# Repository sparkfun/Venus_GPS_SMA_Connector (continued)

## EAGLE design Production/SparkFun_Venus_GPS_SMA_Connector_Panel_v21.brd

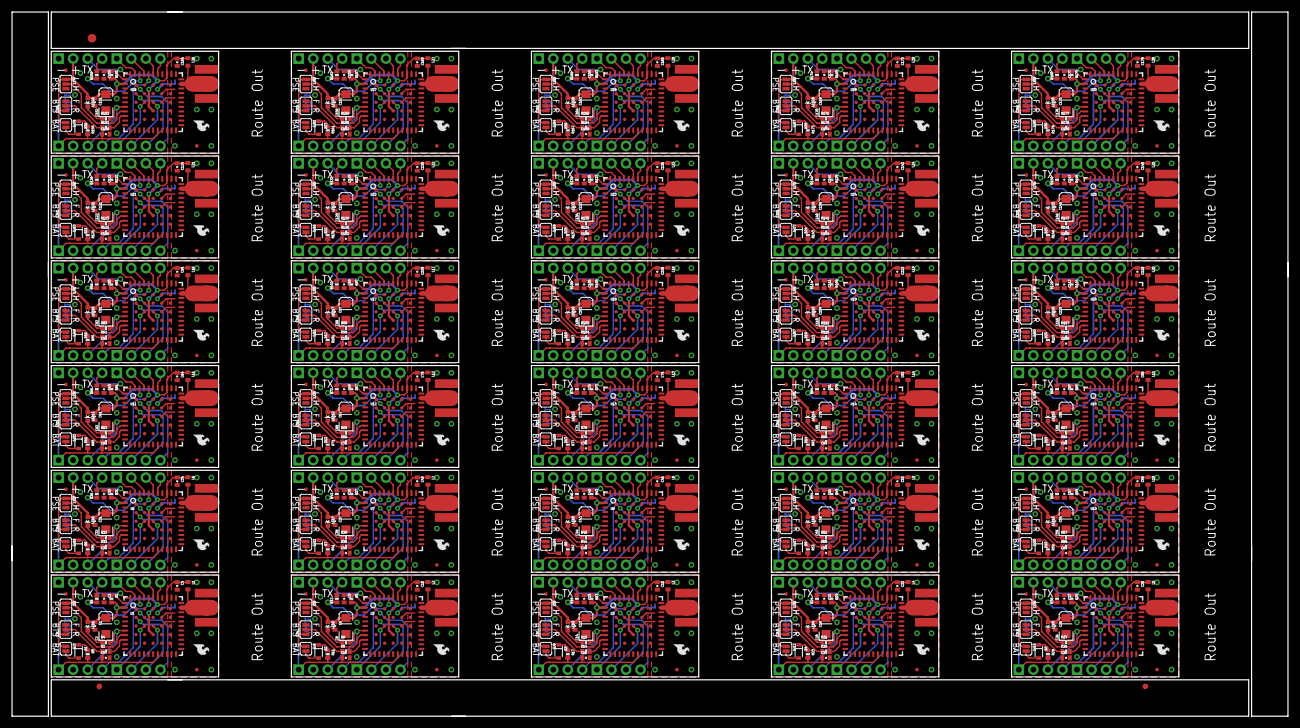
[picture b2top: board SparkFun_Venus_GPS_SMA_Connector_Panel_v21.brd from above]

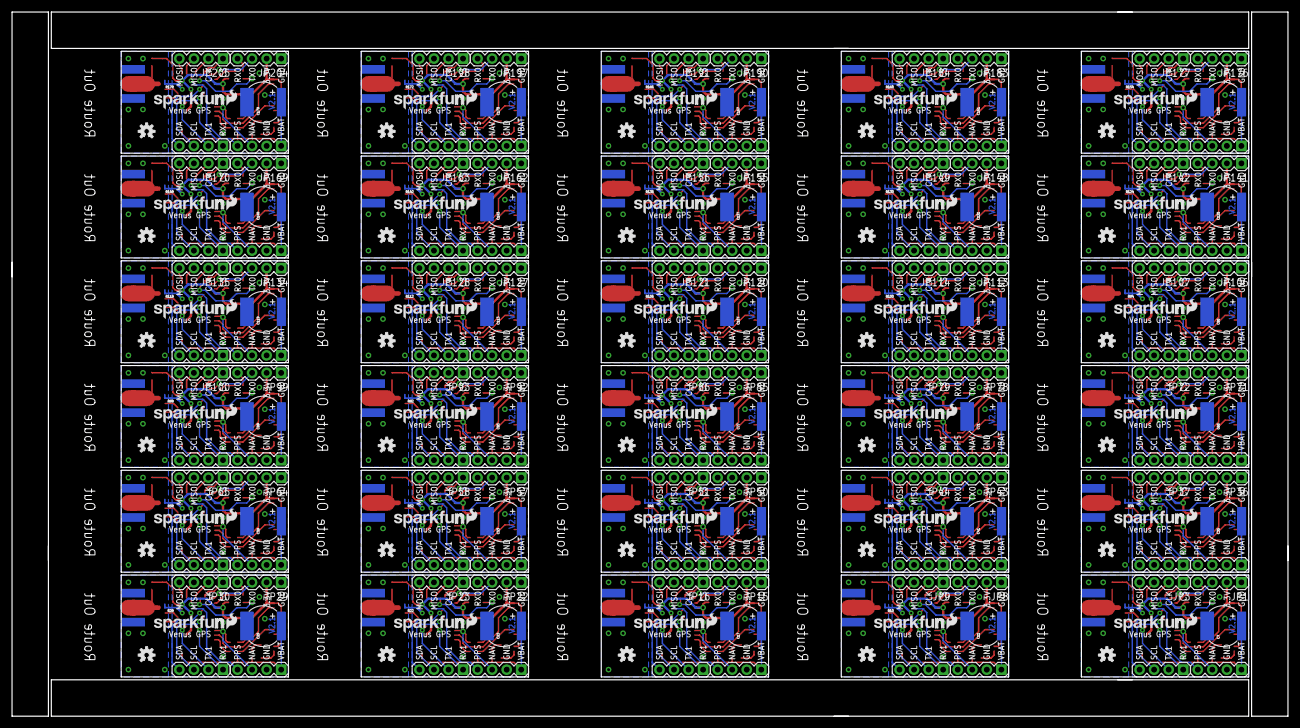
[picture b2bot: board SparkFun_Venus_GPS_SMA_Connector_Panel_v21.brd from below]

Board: 2 copper layers, 222.8 x 122.9 mm, 903 parts (270 on the bottom side), 750 nets.

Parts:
C1, C5, C6, C12, C13, C18, C19, C24, C25, C30, C31, C36, C37, C42, C43, C48, C49, C54, C55, C60, C61, C66, C67, C72, C73, C78, C79, C84, C85, C90, C91, C96, C97, C102, C103, C108, C109, C114, C115, C120, C121, C126, C127, C132, C133, C138, C139, C144, C145, C150, C151, C156, C157, C162, C163, C168, C169, C174, C175, C180: 0.1uF; 0402-CAP
C2, C8, C14, C20, C26, C32, C38, C44, C50, C56, C62, C68, C74, C80, C86, C92, C98, C104, C110, C116, C122, C128, C134, C140, C146, C152, C158, C164, C170, C176: 10uF; EIA3216
C3, C9, C15, C21, C27, C33, C39, C45, C51, C57, C63, C69, C75, C81, C87, C93, C99, C105, C111, C117, C123, C129, C135, C141, C147, C153, C159, C165, C171, C177: 1uF; 0402-CAP
C4, C10, C16, C22, C28, C34, C40, C46, C52, C58, C64, C70, C76, C82, C88, C94, C100, C106, C112, C118, C124, C130, C136, C142, C148, C154, C160, C166, C172, C178: 22pF; 0402-CAP
C7, C11, C17, C23, C29, C35, C41, C47, C53, C59, C65, C71, C77, C83, C89, C95, C101, C107, C113, C119, C125, C131, C137, C143, C149, C155, C161, C167, C173, C179: DNP; EN_J2
D1, D2, D3, D4, D5, D6, D7, D8, D9, D10, D11, D12, D13, D14, D15, D16, D17, D18, D19, D20, D21, D22, D23, D24, D25, D26, D27, D28, D29, D30: BAS16; SOD-323
E$1: FIDUCIAL-1.5X3
E$3, E$4: FIDUCIAL-1X2
JP1, JP8, JP15, JP22, JP29, JP36, JP43, JP50, JP57, JP64, JP71, JP78, JP85, JP92, JP99, JP106, JP113, JP120, JP127, JP134, JP141, JP148, JP155, JP162, JP169, JP176, JP183, JP190, JP197, JP204: MAIN; 1X04
JP2, JP12, JP19, JP26, JP33, JP40, JP47, JP54, JP61, JP68, JP75, JP82, JP89, JP96, JP103, JP110, JP117, JP124, JP131, JP138, JP145, JP152, JP159, JP166, JP173, JP180, JP187, JP194, JP201, JP208: MISC; 1X04
JP3, JP9, JP16, JP23, JP30, JP37, JP44, JP51, JP58, JP65, JP72, JP79, JP86, JP93, JP100, JP107, JP114, JP121, JP128, JP135, JP142, JP149, JP156, JP163, JP170, JP177, JP184, JP191, JP198, JP205: SPI; 1X04
JP4, JP11, JP18, JP25, JP32, JP39, JP46, JP53, JP60, JP67, JP74, JP81, JP88, JP95, JP102, JP109, JP116, JP123, JP130, JP137, JP144, JP151, JP158, JP165, JP172, JP179, JP186, JP193, JP200, JP207: AUX; 1X04
JP5, JP10, JP17, JP24, JP31, JP38, JP45, JP52, JP59, JP66, JP73, JP80, JP87, JP94, JP101, JP108, JP115, JP122, JP129, JP136, JP143, JP150, JP157, JP164, JP171, JP178, JP185, JP192, JP199, JP206: SMA_EDGE; SMA-EDGE
JP6, JP7, JP13, JP14, JP20, JP21, JP27, JP28, JP34, JP35, JP41, JP42, JP48, JP49, JP55, JP56, JP62, JP63, JP69, JP70, JP76, JP77, JP83, JP84, JP90, JP91, JP97, JP98, JP104, JP105, JP111, JP112, JP118, JP119, JP125, JP126, JP132, JP133, JP139, JP140, JP146, JP147, JP153, JP154, JP160, JP161, JP167, JP168, JP174, JP175, JP181, JP182, JP188, JP189, JP195, JP196, JP202, JP203, JP209, JP210: FIDUCIALUFIDUCIAL; MICRO-FIDUCIAL
L1, L2, L3, L4, L5, L6, L7, L8, L9, L10, L11, L12, L13, L14, L15, L16, L17, L18, L19, L20, L21, L22, L23, L24, L25, L26, L27, L28, L29, L30: 33nH; C0402
LED1, LED2, LED3, LED4, LED5, LED6, LED7, LED8, LED9, LED10, LED11, LED12, LED13, LED14, LED15, LED16, LED17, LED18, LED19, LED20, LED21, LED22, LED23, LED24, LED25, LED26, LED27, LED28, LED29, LED30: Red; LED-0603
LOGO1, LOGO2, LOGO4, LOGO6, LOGO7, LOGO9, LOGO10, LOGO12, LOGO13, LOGO15, LOGO16, LOGO18, LOGO19, LOGO21, LOGO22, LOGO24, LOGO25, LOGO27, LOGO28, LOGO30, LOGO31, LOGO33, LOGO34, LOGO36, LOGO37, LOGO39, LOGO40, LOGO42, LOGO43, LOGO45, LOGO46, LOGO48, LOGO49, LOGO51, LOGO52, LOGO54, LOGO55, LOGO57, LOGO58, LOGO60, LOGO61, LOGO63, LOGO64, LOGO66, LOGO67, LOGO69, LOGO70, LOGO72, LOGO73, LOGO75, LOGO76, LOGO78, LOGO79, LOGO81, LOGO82, LOGO84, LOGO85, LOGO87, LOGO88, LOGO90: LOGO-SFESK; SFE-LOGO-FLAME
LOGO3, LOGO5, LOGO8, LOGO11, LOGO14, LOGO17, LOGO20, LOGO23, LOGO26, LOGO29, LOGO32, LOGO35, LOGO38, LOGO41, LOGO44, LOGO47, LOGO50, LOGO53, LOGO56, LOGO59, LOGO62, LOGO65, LOGO68, LOGO71, LOGO74, LOGO77, LOGO80, LOGO83, LOGO86, LOGO89: LOGO-SFENW2; SFE-NEW-WEB
R1, R5, R13, R19, R25, R31, R37, R43, R49, R55, R61, R67, R73, R79, R85, R91, R97, R103, R109, R115, R121, R127, R133, R139, R145, R151, R157, R163, R169, R175: 33k; 0402-RES
R2, R8, R14, R20, R26, R32, R38, R44, R50, R56, R62, R68, R74, R80, R86, R92, R98, R104, R110, R116, R122, R128, R134, R140, R146, R152, R158, R164, R170, R176: 10k; 0402-RES
R3, R4, R9, R11, R15, R17, R21, R23, R27, R29, R33, R35, R39, R41, R45, R47, R51, R53, R57, R59, R63, R65, R69, R71, R75, R77, R81, R83, R87, R89, R93, R95, R99, R101, R105, R107, R111, R113, R117, R119, R123, R125, R129, R131, R135, R137, R141, R143, R147, R149, R153, R155, R159, R161, R165, R167, R171, R173, R177, R179: 330; 0402-RES
R6, R12, R18, R24, R30, R36, R42, R48, R54, R60, R66, R72, R78, R84, R90, R96, R102, R108, R114, R120, R126, R132, R138, R144, R150, R156, R162, R168, R174, R180: 10K; 0402-RES
R7, R10, R16, R22, R28, R34, R40, R46, R52, R58, R64, R70, R76, R82, R88, R94, R100, R106, R112, R118, R124, R130, R136, R142, R148, R154, R160, R166, R172, R178: 0; GND-JUMP
SJ1, SJ4, SJ7, SJ10, SJ13, SJ16, SJ19, SJ22, SJ25, SJ28, SJ31, SJ34, SJ37, SJ40, SJ43, SJ46, SJ49, SJ52, SJ55, SJ58, SJ61, SJ64, SJ67, SJ70, SJ73, SJ76, SJ79, SJ82, SJ85, SJ88: BTS; SJ_3_PASTE2&3
SJ2, SJ5, SJ8, SJ11, SJ14, SJ17, SJ20, SJ23, SJ26, SJ29, SJ32, SJ35, SJ38, SJ41, SJ44, SJ47, SJ50, SJ53, SJ56, SJ59, SJ62, SJ65, SJ68, SJ71, SJ74, SJ77, SJ80, SJ83, SJ86, SJ89: PSE; SJ_3_PASTE2&3
SJ3, SJ6, SJ9, SJ12, SJ15, SJ18, SJ21, SJ24, SJ27, SJ30, SJ33, SJ36, SJ39, SJ42, SJ45, SJ48, SJ51, SJ54, SJ57, SJ60, SJ63, SJ66, SJ69, SJ72, SJ75, SJ78, SJ81, SJ84, SJ87, SJ90: BAT; SJ_2S
U1, U2, U3, U4, U5, U6, U7, U8, U9, U10, U11, U12, U13, U14, U15, U16, U17, U18, U19, U20, U21, U22, U23, U24, U25, U26, U27, U28, U29, U30: VENUS638FLPX-L; VENUS638FLPX
U$1, U$2, U$3, U$4, U$5, U$6, U$7, U$8, U$9, U$10, U$11, U$12, U$13, U$14, U$15, U$16, U$17, U$18, U$19, U$20, U$21, U$22, U$23, U$24, U$25, U$26, U$27, U$28, U$29, U$30: OSHW-LOGOS; OSHW-LOGO-S

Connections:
3.3V: C1.1, C2.A, C4.1, JP1.2, L1.1, LED1.A, R1.2, SJ1.1, SJ2.1, SJ3.1, U1.2, U1.36, U1.58
3.3V1: C6.1, C8.A, C10.1, JP8.2, L2.1, LED2.A, R5.2, SJ4.1, SJ5.1, SJ6.1, U2.2, U2.36, U2.58
3.3V2: C13.1, C14.A, C16.1, JP15.2, L3.1, LED3.A, R13.2, SJ7.1, SJ8.1, SJ9.1, U3.2, U3.36, U3.58
3.3V3: C19.1, C20.A, C22.1, JP22.2, L4.1, LED4.A, R19.2, SJ10.1, SJ11.1, SJ12.1, U4.2, U4.36, U4.58
3.3V4: C25.1, C26.A, C28.1, JP29.2, L5.1, LED5.A, R25.2, SJ13.1, SJ14.1, SJ15.1, U5.2, U5.36, U5.58
3.3V5: C31.1, C32.A, C34.1, JP36.2, L6.1, LED6.A, R31.2, SJ16.1, SJ17.1, SJ18.1, U6.2, U6.36, U6.58
3.3V6: C37.1, C38.A, C40.1, JP43.2, L7.1, LED7.A, R37.2, SJ19.1, SJ20.1, SJ21.1, U7.2, U7.36, U7.58
3.3V7: C43.1, C44.A, C46.1, JP50.2, L8.1, LED8.A, R43.2, SJ22.1, SJ23.1, SJ24.1, U8.2, U8.36, U8.58
3.3V8: C49.1, C50.A, C52.1, JP57.2, L9.1, LED9.A, R49.2, SJ25.1, SJ26.1, SJ27.1, U9.2, U9.36, U9.58
3.3V9: C55.1, C56.A, C58.1, JP64.2, L10.1, LED10.A, R55.2, SJ28.1, SJ29.1, SJ30.1, U10.2, U10.36, U10.58
3.3V10: C61.1, C62.A, C64.1, JP71.2, L11.1, LED11.A, R61.2, SJ31.1, SJ32.1, SJ33.1, U11.2, U11.36, U11.58
3.3V11: C67.1, C68.A, C70.1, JP78.2, L12.1, LED12.A, R67.2, SJ34.1, SJ35.1, SJ36.1, U12.2, U12.36, U12.58
3.3V12: C73.1, C74.A, C76.1, JP85.2, L13.1, LED13.A, R73.2, SJ37.1, SJ38.1, SJ39.1, U13.2, U13.36, U13.58
3.3V13: C79.1, C80.A, C82.1, JP92.2, L14.1, LED14.A, R79.2, SJ40.1, SJ41.1, SJ42.1, U14.2, U14.36, U14.58
3.3V14: C85.1, C86.A, C88.1, JP99.2, L15.1, LED15.A, R85.2, SJ43.1, SJ44.1, SJ45.1, U15.2, U15.36, U15.58
3.3V15: C91.1, C92.A, C94.1, JP106.2, L16.1, LED16.A, R91.2, SJ46.1, SJ47.1, SJ48.1, U16.2, U16.36, U16.58
3.3V16: C97.1, C98.A, C100.1, JP113.2, L17.1, LED17.A, R97.2, SJ49.1, SJ50.1, SJ51.1, U17.2, U17.36, U17.58
3.3V17: C103.1, C104.A, C106.1, JP120.2, L18.1, LED18.A, R103.2, SJ52.1, SJ53.1, SJ54.1, U18.2, U18.36, U18.58
3.3V18: C109.1, C110.A, C112.1, JP127.2, L19.1, LED19.A, R109.2, SJ55.1, SJ56.1, SJ57.1, U19.2, U19.36, U19.58
3.3V19: C115.1, C116.A, C118.1, JP134.2, L20.1, LED20.A, R115.2, SJ58.1, SJ59.1, SJ60.1, U20.2, U20.36, U20.58
3.3V20: C121.1, C122.A, C124.1, JP141.2, L21.1, LED21.A, R121.2, SJ61.1, SJ62.1, SJ63.1, U21.2, U21.36, U21.58
3.3V21: C127.1, C128.A, C130.1, JP148.2, L22.1, LED22.A, R127.2, SJ64.1, SJ65.1, SJ66.1, U22.2, U22.36, U22.58
3.3V22: C133.1, C134.A, C136.1, JP155.2, L23.1, LED23.A, R133.2, SJ67.1, SJ68.1, SJ69.1, U23.2, U23.36, U23.58
3.3V23: C139.1, C140.A, C142.1, JP162.2, L24.1, LED24.A, R139.2, SJ70.1, SJ71.1, SJ72.1, U24.2, U24.36, U24.58
3.3V24: C145.1, C146.A, C148.1, JP169.2, L25.1, LED25.A, R145.2, SJ73.1, SJ74.1, SJ75.1, U25.2, U25.36, U25.58
3.3V25: C151.1, C152.A, C154.1, JP176.2, L26.1, LED26.A, R151.2, SJ76.1, SJ77.1, SJ78.1, U26.2, U26.36, U26.58
3.3V26: C157.1, C158.A, C160.1, JP183.2, L27.1, LED27.A, R157.2, SJ79.1, SJ80.1, SJ81.1, U27.2, U27.36, U27.58
3.3V27: C163.1, C164.A, C166.1, JP190.2, L28.1, LED28.A, R163.2, SJ82.1, SJ83.1, SJ84.1, U28.2, U28.36, U28.58
3.3V28: C169.1, C170.A, C172.1, JP197.2, L29.1, LED29.A, R169.2, SJ85.1, SJ86.1, SJ87.1, U29.2, U29.36, U29.58
3.3V29: C175.1, C176.A, C178.1, JP204.2, L30.1, LED30.A, R175.2, SJ88.1, SJ89.1, SJ90.1, U30.2, U30.36, U30.58
ANT: JP5.SIG, L1.2, U1.32
ANT1: JP10.SIG, L2.2, U2.32
ANT2: JP17.SIG, L3.2, U3.32
ANT3: JP24.SIG, L4.2, U4.32
ANT4: JP31.SIG, L5.2, U5.32
ANT5: JP38.SIG, L6.2, U6.32
ANT6: JP45.SIG, L7.2, U7.32
ANT7: JP52.SIG, L8.2, U8.32
ANT8: JP59.SIG, L9.2, U9.32
ANT9: JP66.SIG, L10.2, U10.32
ANT10: JP73.SIG, L11.2, U11.32
ANT11: JP80.SIG, L12.2, U12.32
ANT12: JP87.SIG, L13.2, U13.32
ANT13: JP94.SIG, L14.2, U14.32
ANT14: JP101.SIG, L15.2, U15.32
ANT15: JP108.SIG, L16.2, U16.32
ANT16: JP115.SIG, L17.2, U17.32
ANT17: JP122.SIG, L18.2, U18.32
ANT18: JP129.SIG, L19.2, U19.32
ANT19: JP136.SIG, L20.2, U20.32
ANT20: JP143.SIG, L21.2, U21.32
ANT21: JP150.SIG, L22.2, U22.32
ANT22: JP157.SIG, L23.2, U23.32
ANT23: JP164.SIG, L24.2, U24.32
ANT24: JP171.SIG, L25.2, U25.32
ANT25: JP178.SIG, L26.2, U26.32
ANT26: JP185.SIG, L27.2, U27.32
ANT27: JP192.SIG, L28.2, U28.32
ANT28: JP199.SIG, L29.2, U29.32
ANT29: JP206.SIG, L30.2, U30.32
BOOT_SEL: R2.2, U1.9
BOOT_SEL1: R8.2, U2.9
BOOT_SEL2: R14.2, U3.9
BOOT_SEL3: R20.2, U4.9
BOOT_SEL4: R26.2, U5.9
BOOT_SEL5: R32.2, U6.9
BOOT_SEL6: R38.2, U7.9
BOOT_SEL7: R44.2, U8.9
BOOT_SEL8: R50.2, U9.9
BOOT_SEL9: R56.2, U10.9
BOOT_SEL10: R62.2, U11.9
BOOT_SEL11: R68.2, U12.9
BOOT_SEL12: R74.2, U13.9
BOOT_SEL13: R80.2, U14.9
BOOT_SEL14: R86.2, U15.9
BOOT_SEL15: R92.2, U16.9
BOOT_SEL16: R98.2, U17.9
BOOT_SEL17: R104.2, U18.9
BOOT_SEL18: R110.2, U19.9
BOOT_SEL19: R116.2, U20.9
BOOT_SEL20: R122.2, U21.9
BOOT_SEL21: R128.2, U22.9
BOOT_SEL22: R134.2, U23.9
BOOT_SEL23: R140.2, U24.9
BOOT_SEL24: R146.2, U25.9
BOOT_SEL25: R152.2, U26.9
BOOT_SEL26: R158.2, U27.9
BOOT_SEL27: R164.2, U28.9
BOOT_SEL28: R170.2, U29.9
BOOT_SEL29: R176.2, U30.9
CLK: JP3.2, U1.41
CLK1: JP9.2, U2.41
CLK2: JP16.2, U3.41
CLK3: JP23.2, U4.41
CLK4: JP30.2, U5.41
CLK5: JP37.2, U6.41
CLK6: JP44.2, U7.41
CLK7: JP51.2, U8.41
CLK8: JP58.2, U9.41
CLK9: JP65.2, U10.41
CLK10: JP72.2, U11.41
CLK11: JP79.2, U12.41
CLK12: JP86.2, U13.41
CLK13: JP93.2, U14.41
CLK14: JP100.2, U15.41
CLK15: JP107.2, U16.41
CLK16: JP114.2, U17.41
CLK17: JP121.2, U18.41
CLK18: JP128.2, U19.41
CLK19: JP135.2, U20.41
CLK20: JP142.2, U21.41
CLK21: JP149.2, U22.41
CLK22: JP156.2, U23.41
CLK23: JP163.2, U24.41
CLK24: JP170.2, U25.41
CLK25: JP177.2, U26.41
CLK26: JP184.2, U27.41
CLK27: JP191.2, U28.41
CLK28: JP198.2, U29.41
CLK29: JP205.2, U30.41
CS: JP3.1, U1.43
CS1: JP9.1, U2.43
CS2: JP16.1, U3.43
CS3: JP23.1, U4.43
CS4: JP30.1, U5.43
CS5: JP37.1, U6.43
CS6: JP44.1, U7.43
CS7: JP51.1, U8.43
CS8: JP58.1, U9.43
CS9: JP65.1, U10.43
CS10: JP72.1, U11.43
CS11: JP79.1, U12.43
CS12: JP86.1, U13.43
CS13: JP93.1, U14.43
CS14: JP100.1, U15.43
CS15: JP107.1, U16.43
CS16: JP114.1, U17.43
CS17: JP121.1, U18.43
CS18: JP128.1, U19.43
CS19: JP135.1, U20.43
CS20: JP142.1, U21.43
CS21: JP149.1, U22.43
CS22: JP156.1, U23.43
CS23: JP163.1, U24.43
CS24: JP170.1, U25.43
CS25: JP177.1, U26.43
CS26: JP184.1, U27.43
CS27: JP191.1, U28.43
CS28: JP198.1, U29.43
CS29: JP205.1, U30.43
GND: C1.2, C2.C, C3.2, C5.2, C7.-, JP1.1, JP2.2, R7.1, SJ1.3, SJ2.3, U1.10, U1.11, U1.15, U1.19, U1.49, U1.60, U1.64
GND1: C6.2, C8.C, C9.2, C11.-, C12.2, JP8.1, JP12.2, R10.1, SJ4.3, SJ5.3, U2.10, U2.11, U2.15, U2.19, U2.49, U2.60, U2.64
GND2: C13.2, C14.C, C15.2, C17.-, C18.2, JP15.1, JP19.2, R16.1, SJ7.3, SJ8.3, U3.10, U3.11, U3.15, U3.19, U3.49, U3.60, U3.64
GND3: C19.2, C20.C, C21.2, C23.-, C24.2, JP22.1, JP26.2, R22.1, SJ10.3, SJ11.3, U4.10, U4.11, U4.15, U4.19, U4.49, U4.60, U4.64
GND4: C25.2, C26.C, C27.2, C29.-, C30.2, JP29.1, JP33.2, R28.1, SJ13.3, SJ14.3, U5.10, U5.11, U5.15, U5.19, U5.49, U5.60, U5.64
GND5: C31.2, C32.C, C33.2, C35.-, C36.2, JP36.1, JP40.2, R34.1, SJ16.3, SJ17.3, U6.10, U6.11, U6.15, U6.19, U6.49, U6.60, U6.64
GND6: C37.2, C38.C, C39.2, C41.-, C42.2, JP43.1, JP47.2, R40.1, SJ19.3, SJ20.3, U7.10, U7.11, U7.15, U7.19, U7.49, U7.60, U7.64
GND7: C43.2, C44.C, C45.2, C47.-, C48.2, JP50.1, JP54.2, R46.1, SJ22.3, SJ23.3, U8.10, U8.11, U8.15, U8.19, U8.49, U8.60, U8.64
GND8: C49.2, C50.C, C51.2, C53.-, C54.2, JP57.1, JP61.2, R52.1, SJ25.3, SJ26.3, U9.10, U9.11, U9.15, U9.19, U9.49, U9.60, U9.64
GND9: C55.2, C56.C, C57.2, C59.-, C60.2, JP64.1, JP68.2, R58.1, SJ28.3, SJ29.3, U10.10, U10.11, U10.15, U10.19, U10.49, U10.60, U10.64
GND10: C61.2, C62.C, C63.2, C65.-, C66.2, JP71.1, JP75.2, R64.1, SJ31.3, SJ32.3, U11.10, U11.11, U11.15, U11.19, U11.49, U11.60, U11.64
GND11: C67.2, C68.C, C69.2, C71.-, C72.2, JP78.1, JP82.2, R70.1, SJ34.3, SJ35.3, U12.10, U12.11, U12.15, U12.19, U12.49, U12.60, U12.64
GND12: C73.2, C74.C, C75.2, C77.-, C78.2, JP85.1, JP89.2, R76.1, SJ37.3, SJ38.3, U13.10, U13.11, U13.15, U13.19, U13.49, U13.60, U13.64
GND13: C79.2, C80.C, C81.2, C83.-, C84.2, JP92.1, JP96.2, R82.1, SJ40.3, SJ41.3, U14.10, U14.11, U14.15, U14.19, U14.49, U14.60, U14.64
GND14: C85.2, C86.C, C87.2, C89.-, C90.2, JP99.1, JP103.2, R88.1, SJ43.3, SJ44.3, U15.10, U15.11, U15.15, U15.19, U15.49, U15.60, U15.64
GND15: C91.2, C92.C, C93.2, C95.-, C96.2, JP106.1, JP110.2, R94.1, SJ46.3, SJ47.3, U16.10, U16.11, U16.15, U16.19, U16.49, U16.60, U16.64
GND16: C97.2, C98.C, C99.2, C101.-, C102.2, JP113.1, JP117.2, R100.1, SJ49.3, SJ50.3, U17.10, U17.11, U17.15, U17.19, U17.49, U17.60, U17.64
GND17: C103.2, C104.C, C105.2, C107.-, C108.2, JP120.1, JP124.2, R106.1, SJ52.3, SJ53.3, U18.10, U18.11, U18.15, U18.19, U18.49, U18.60, U18.64
GND18: C109.2, C110.C, C111.2, C113.-, C114.2, JP127.1, JP131.2, R112.1, SJ55.3, SJ56.3, U19.10, U19.11, U19.15, U19.19, U19.49, U19.60, U19.64
GND19: C115.2, C116.C, C117.2, C119.-, C120.2, JP134.1, JP138.2, R118.1, SJ58.3, SJ59.3, U20.10, U20.11, U20.15, U20.19, U20.49, U20.60, U20.64
GND20: C121.2, C122.C, C123.2, C125.-, C126.2, JP141.1, JP145.2, R124.1, SJ61.3, SJ62.3, U21.10, U21.11, U21.15, U21.19, U21.49, U21.60, U21.64
GND21: C127.2, C128.C, C129.2, C131.-, C132.2, JP148.1, JP152.2, R130.1, SJ64.3, SJ65.3, U22.10, U22.11, U22.15, U22.19, U22.49, U22.60, U22.64
GND22: C133.2, C134.C, C135.2, C137.-, C138.2, JP155.1, JP159.2, R136.1, SJ67.3, SJ68.3, U23.10, U23.11, U23.15, U23.19, U23.49, U23.60, U23.64
GND23: C139.2, C140.C, C141.2, C143.-, C144.2, JP162.1, JP166.2, R142.1, SJ70.3, SJ71.3, U24.10, U24.11, U24.15, U24.19, U24.49, U24.60, U24.64
GND24: C145.2, C146.C, C147.2, C149.-, C150.2, JP169.1, JP173.2, R148.1, SJ73.3, SJ74.3, U25.10, U25.11, U25.15, U25.19, U25.49, U25.60, U25.64
GND25: C151.2, C152.C, C153.2, C155.-, C156.2, JP176.1, JP180.2, R154.1, SJ76.3, SJ77.3, U26.10, U26.11, U26.15, U26.19, U26.49, U26.60, U26.64
GND26: C157.2, C158.C, C159.2, C161.-, C162.2, JP183.1, JP187.2, R160.1, SJ79.3, SJ80.3, U27.10, U27.11, U27.15, U27.19, U27.49, U27.60, U27.64
GND27: C163.2, C164.C, C165.2, C167.-, C168.2, JP190.1, JP194.2, R166.1, SJ82.3, SJ83.3, U28.10, U28.11, U28.15, U28.19, U28.49, U28.60, U28.64
GND28: C169.2, C170.C, C171.2, C173.-, C174.2, JP197.1, JP201.2, R172.1, SJ85.3, SJ86.3, U29.10, U29.11, U29.15, U29.19, U29.49, U29.60, U29.64
GND29: C175.2, C176.C, C177.2, C179.-, C180.2, JP204.1, JP208.2, R178.1, SJ88.3, SJ89.3, U30.10, U30.11, U30.15, U30.19, U30.49, U30.60, U30.64
MISO: JP3.3, U1.39
MISO1: JP9.3, U2.39
MISO2: JP16.3, U3.39
MISO3: JP23.3, U4.39
MISO4: JP30.3, U5.39
MISO5: JP37.3, U6.39
MISO6: JP44.3, U7.39
MISO7: JP51.3, U8.39
MISO8: JP58.3, U9.39
MISO9: JP65.3, U10.39
MISO10: JP72.3, U11.39
MISO11: JP79.3, U12.39
MISO12: JP86.3, U13.39
MISO13: JP93.3, U14.39
MISO14: JP100.3, U15.39
MISO15: JP107.3, U16.39
MISO16: JP114.3, U17.39
MISO17: JP121.3, U18.39
MISO18: JP128.3, U19.39
MISO19: JP135.3, U20.39
MISO20: JP142.3, U21.39
MISO21: JP149.3, U22.39
MISO22: JP156.3, U23.39
MISO23: JP163.3, U24.39
MISO24: JP170.3, U25.39
MISO25: JP177.3, U26.39
MISO26: JP184.3, U27.39
MISO27: JP191.3, U28.39
MISO28: JP198.3, U29.39
MISO29: JP205.3, U30.39
MOSI: JP3.4, U1.38
MOSI1: JP9.4, U2.38
MOSI2: JP16.4, U3.38
MOSI3: JP23.4, U4.38
MOSI4: JP30.4, U5.38
MOSI5: JP37.4, U6.38
MOSI6: JP44.4, U7.38
MOSI7: JP51.4, U8.38
MOSI8: JP58.4, U9.38
MOSI9: JP65.4, U10.38
MOSI10: JP72.4, U11.38
MOSI11: JP79.4, U12.38
MOSI12: JP86.4, U13.38
MOSI13: JP93.4, U14.38
MOSI14: JP100.4, U15.38
MOSI15: JP107.4, U16.38
MOSI16: JP114.4, U17.38
MOSI17: JP121.4, U18.38
MOSI18: JP128.4, U19.38
MOSI19: JP135.4, U20.38
MOSI20: JP142.4, U21.38
MOSI21: JP149.4, U22.38
MOSI22: JP156.4, U23.38
MOSI23: JP163.4, U24.38
MOSI24: JP170.4, U25.38
MOSI25: JP177.4, U26.38
MOSI26: JP184.4, U27.38
MOSI27: JP191.4, U28.38
MOSI28: JP198.4, U29.38
MOSI29: JP205.4, U30.38
unnamed: LED1.C, R4.1
unnamed: R2.1, SJ1.2
unnamed: D1.1, R3.1
unnamed: LED2.C, R9.1
unnamed: R8.1, SJ4.2
unnamed: D1.2, SJ3.2
unnamed: D2.2, SJ6.2
unnamed: D2.1, R11.1
unnamed: LED3.C, R15.1
unnamed: R14.1, SJ7.2
unnamed: D3.2, SJ9.2
unnamed: D3.1, R17.1
unnamed: LED4.C, R21.1
unnamed: R20.1, SJ10.2
unnamed: D4.2, SJ12.2
unnamed: D4.1, R23.1
unnamed: LED5.C, R27.1
unnamed: R26.1, SJ13.2
unnamed: D5.2, SJ15.2
unnamed: D5.1, R29.1
unnamed: LED6.C, R33.1
unnamed: R32.1, SJ16.2
unnamed: D6.2, SJ18.2
unnamed: D6.1, R35.1
unnamed: LED7.C, R39.1
unnamed: R38.1, SJ19.2
unnamed: D7.2, SJ21.2
unnamed: D7.1, R41.1
unnamed: LED8.C, R45.1
unnamed: R44.1, SJ22.2
unnamed: D8.2, SJ24.2
unnamed: D8.1, R47.1
unnamed: LED9.C, R51.1
unnamed: R50.1, SJ25.2
unnamed: D9.2, SJ27.2
unnamed: D9.1, R53.1
unnamed: LED10.C, R57.1
unnamed: R56.1, SJ28.2
unnamed: D10.2, SJ30.2
unnamed: D10.1, R59.1
unnamed: LED11.C, R63.1
unnamed: R62.1, SJ31.2
unnamed: D11.2, SJ33.2
unnamed: D11.1, R65.1
unnamed: LED12.C, R69.1
unnamed: R68.1, SJ34.2
unnamed: D12.2, SJ36.2
unnamed: D12.1, R71.1
unnamed: LED13.C, R75.1
unnamed: R74.1, SJ37.2
unnamed: D13.2, SJ39.2
unnamed: D13.1, R77.1
unnamed: LED14.C, R81.1
unnamed: R80.1, SJ40.2
unnamed: D14.2, SJ42.2
unnamed: D14.1, R83.1
unnamed: LED15.C, R87.1
unnamed: R86.1, SJ43.2
unnamed: D15.2, SJ45.2
unnamed: D15.1, R89.1
unnamed: LED16.C, R93.1
unnamed: R92.1, SJ46.2
unnamed: D16.2, SJ48.2
unnamed: D16.1, R95.1
unnamed: LED17.C, R99.1
unnamed: R98.1, SJ49.2
unnamed: D17.2, SJ51.2
unnamed: D17.1, R101.1
unnamed: LED18.C, R105.1
unnamed: R104.1, SJ52.2
unnamed: D18.2, SJ54.2
unnamed: D18.1, R107.1
unnamed: LED19.C, R111.1
unnamed: R110.1, SJ55.2
unnamed: D19.2, SJ57.2
unnamed: D19.1, R113.1
unnamed: LED20.C, R117.1
unnamed: R116.1, SJ58.2
unnamed: D20.2, SJ60.2
unnamed: D20.1, R119.1
unnamed: LED21.C, R123.1
unnamed: R122.1, SJ61.2
unnamed: D21.2, SJ63.2
unnamed: D21.1, R125.1
unnamed: LED22.C, R129.1
unnamed: R128.1, SJ64.2
unnamed: D22.2, SJ66.2
unnamed: D22.1, R131.1
unnamed: LED23.C, R135.1
unnamed: R134.1, SJ67.2
unnamed: D23.2, SJ69.2
unnamed: D23.1, R137.1
unnamed: LED24.C, R141.1
unnamed: R140.1, SJ70.2
unnamed: D24.2, SJ72.2
unnamed: D24.1, R143.1
unnamed: LED25.C, R147.1
unnamed: R146.1, SJ73.2
unnamed: D25.2, SJ75.2
unnamed: D25.1, R149.1
unnamed: LED26.C, R153.1
unnamed: R152.1, SJ76.2
unnamed: D26.2, SJ78.2
unnamed: D26.1, R155.1
unnamed: LED27.C, R159.1
unnamed: R158.1, SJ79.2
unnamed: D27.2, SJ81.2
unnamed: D27.1, R161.1
unnamed: LED28.C, R165.1
unnamed: R164.1, SJ82.2
unnamed: D28.2, SJ84.2
unnamed: D28.1, R167.1
unnamed: LED29.C, R171.1
unnamed: R170.1, SJ85.2
unnamed: D29.2, SJ87.2
unnamed: D29.1, R173.1
unnamed: LED30.C, R177.1
unnamed: R176.1, SJ88.2
unnamed: D30.2, SJ90.2
unnamed: D30.1, R179.1
NAV: JP2.3, R4.2, U1.7
NAV1: JP12.3, R9.2, U2.7
NAV2: JP19.3, R15.2, U3.7
NAV3: JP26.3, R21.2, U4.7
NAV4: JP33.3, R27.2, U5.7
NAV5: JP40.3, R33.2, U6.7
NAV6: JP47.3, R39.2, U7.7
NAV7: JP54.3, R45.2, U8.7
NAV8: JP61.3, R51.2, U9.7
NAV9: JP68.3, R57.2, U10.7
NAV10: JP75.3, R63.2, U11.7
NAV11: JP82.3, R69.2, U12.7
NAV12: JP89.3, R75.2, U13.7
NAV13: JP96.3, R81.2, U14.7
NAV14: JP103.3, R87.2, U15.7
NAV15: JP110.3, R93.2, U16.7
NAV16: JP117.3, R99.2, U17.7
NAV17: JP124.3, R105.2, U18.7
NAV18: JP131.3, R111.2, U19.7
NAV19: JP138.3, R117.2, U20.7
NAV20: JP145.3, R123.2, U21.7
NAV21: JP152.3, R129.2, U22.7
NAV22: JP159.3, R135.2, U23.7
NAV23: JP166.3, R141.2, U24.7
NAV24: JP173.3, R147.2, U25.7
NAV25: JP180.3, R153.2, U26.7
NAV26: JP187.3, R159.2, U27.7
NAV27: JP194.3, R165.2, U28.7
NAV28: JP201.3, R171.2, U29.7
NAV29: JP208.3, R177.2, U30.7
PPS: JP2.4, U1.40
PPS1: JP12.4, U2.40
PPS2: JP19.4, U3.40
PPS3: JP26.4, U4.40
PPS4: JP33.4, U5.40
PPS5: JP40.4, U6.40
PPS6: JP47.4, U7.40
PPS7: JP54.4, U8.40
PPS8: JP61.4, U9.40
PPS9: JP68.4, U10.40
PPS10: JP75.4, U11.40
PPS11: JP82.4, U12.40
PPS12: JP89.4, U13.40
PPS13: JP96.4, U14.40
PPS14: JP103.4, U15.40
PPS15: JP110.4, U16.40
PPS16: JP117.4, U17.40
PPS17: JP124.4, U18.40
PPS18: JP131.4, U19.40
PPS19: JP138.4, U20.40
PPS20: JP145.4, U21.40
PPS21: JP152.4, U22.40
PPS22: JP159.4, U23.40
PPS23: JP166.4, U24.40
PPS24: JP173.4, U25.40
PPS25: JP180.4, U26.40
PPS26: JP187.4, U27.40
PPS27: JP194.4, U28.40
PPS28: JP201.4, U29.40
PPS29: JP208.4, U30.40
PSE_SEL: SJ2.2, U1.8
PSE_SEL1: SJ5.2, U2.8
PSE_SEL2: SJ8.2, U3.8
PSE_SEL3: SJ11.2, U4.8
PSE_SEL4: SJ14.2, U5.8
PSE_SEL5: SJ17.2, U6.8
PSE_SEL6: SJ20.2, U7.8
PSE_SEL7: SJ23.2, U8.8
PSE_SEL8: SJ26.2, U9.8
PSE_SEL9: SJ29.2, U10.8
PSE_SEL10: SJ32.2, U11.8
PSE_SEL11: SJ35.2, U12.8
PSE_SEL12: SJ38.2, U13.8
PSE_SEL13: SJ41.2, U14.8
PSE_SEL14: SJ44.2, U15.8
PSE_SEL15: SJ47.2, U16.8
PSE_SEL16: SJ50.2, U17.8
PSE_SEL17: SJ53.2, U18.8
PSE_SEL18: SJ56.2, U19.8
PSE_SEL19: SJ59.2, U20.8
PSE_SEL20: SJ62.2, U21.8
PSE_SEL21: SJ65.2, U22.8
PSE_SEL22: SJ68.2, U23.8
PSE_SEL23: SJ71.2, U24.8
PSE_SEL24: SJ74.2, U25.8
PSE_SEL25: SJ77.2, U26.8
PSE_SEL26: SJ80.2, U27.8
PSE_SEL27: SJ83.2, U28.8
PSE_SEL28: SJ86.2, U29.8
PSE_SEL29: SJ89.2, U30.8
RFGND: C4.2, JP5.GND@0, JP5.GND@1, JP5.GND@2, JP5.GND@3, R7.2, U1.21, U1.22, U1.24, U1.25, U1.27, U1.28, U1.29, U1.31, U1.33, U1.61, U1.62, U1.65, U1.69
RFGND1: C10.2, JP10.GND@0, JP10.GND@1, JP10.GND@2, JP10.GND@3, R10.2, U2.21, U2.22, U2.24, U2.25, U2.27, U2.28, U2.29, U2.31, U2.33, U2.61, U2.62, U2.65, U2.69
RFGND2: C16.2, JP17.GND@0, JP17.GND@1, JP17.GND@2, JP17.GND@3, R16.2, U3.21, U3.22, U3.24, U3.25, U3.27, U3.28, U3.29, U3.31, U3.33, U3.61, U3.62, U3.65, U3.69
RFGND3: C22.2, JP24.GND@0, JP24.GND@1, JP24.GND@2, JP24.GND@3, R22.2, U4.21, U4.22, U4.24, U4.25, U4.27, U4.28, U4.29, U4.31, U4.33, U4.61, U4.62, U4.65, U4.69
RFGND4: C28.2, JP31.GND@0, JP31.GND@1, JP31.GND@2, JP31.GND@3, R28.2, U5.21, U5.22, U5.24, U5.25, U5.27, U5.28, U5.29, U5.31, U5.33, U5.61, U5.62, U5.65, U5.69
RFGND5: C34.2, JP38.GND@0, JP38.GND@1, JP38.GND@2, JP38.GND@3, R34.2, U6.21, U6.22, U6.24, U6.25, U6.27, U6.28, U6.29, U6.31, U6.33, U6.61, U6.62, U6.65, U6.69
RFGND6: C40.2, JP45.GND@0, JP45.GND@1, JP45.GND@2, JP45.GND@3, R40.2, U7.21, U7.22, U7.24, U7.25, U7.27, U7.28, U7.29, U7.31, U7.33, U7.61, U7.62, U7.65, U7.69
RFGND7: C46.2, JP52.GND@0, JP52.GND@1, JP52.GND@2, JP52.GND@3, R46.2, U8.21, U8.22, U8.24, U8.25, U8.27, U8.28, U8.29, U8.31, U8.33, U8.61, U8.62, U8.65, U8.69
RFGND8: C52.2, JP59.GND@0, JP59.GND@1, JP59.GND@2, JP59.GND@3, R52.2, U9.21, U9.22, U9.24, U9.25, U9.27, U9.28, U9.29, U9.31, U9.33, U9.61, U9.62, U9.65, U9.69
RFGND9: C58.2, JP66.GND@0, JP66.GND@1, JP66.GND@2, JP66.GND@3, R58.2, U10.21, U10.22, U10.24, U10.25, U10.27, U10.28, U10.29, U10.31, U10.33, U10.61, U10.62, U10.65, U10.69
RFGND10: C64.2, JP73.GND@0, JP73.GND@1, JP73.GND@2, JP73.GND@3, R64.2, U11.21, U11.22, U11.24, U11.25, U11.27, U11.28, U11.29, U11.31, U11.33, U11.61, U11.62, U11.65, U11.69
RFGND11: C70.2, JP80.GND@0, JP80.GND@1, JP80.GND@2, JP80.GND@3, R70.2, U12.21, U12.22, U12.24, U12.25, U12.27, U12.28, U12.29, U12.31, U12.33, U12.61, U12.62, U12.65, U12.69
RFGND12: C76.2, JP87.GND@0, JP87.GND@1, JP87.GND@2, JP87.GND@3, R76.2, U13.21, U13.22, U13.24, U13.25, U13.27, U13.28, U13.29, U13.31, U13.33, U13.61, U13.62, U13.65, U13.69
RFGND13: C82.2, JP94.GND@0, JP94.GND@1, JP94.GND@2, JP94.GND@3, R82.2, U14.21, U14.22, U14.24, U14.25, U14.27, U14.28, U14.29, U14.31, U14.33, U14.61, U14.62, U14.65, U14.69
RFGND14: C88.2, JP101.GND@0, JP101.GND@1, JP101.GND@2, JP101.GND@3, R88.2, U15.21, U15.22, U15.24, U15.25, U15.27, U15.28, U15.29, U15.31, U15.33, U15.61, U15.62, U15.65, U15.69
RFGND15: C94.2, JP108.GND@0, JP108.GND@1, JP108.GND@2, JP108.GND@3, R94.2, U16.21, U16.22, U16.24, U16.25, U16.27, U16.28, U16.29, U16.31, U16.33, U16.61, U16.62, U16.65, U16.69
RFGND16: C100.2, JP115.GND@0, JP115.GND@1, JP115.GND@2, JP115.GND@3, R100.2, U17.21, U17.22, U17.24, U17.25, U17.27, U17.28, U17.29, U17.31, U17.33, U17.61, U17.62, U17.65, U17.69
RFGND17: C106.2, JP122.GND@0, JP122.GND@1, JP122.GND@2, JP122.GND@3, R106.2, U18.21, U18.22, U18.24, U18.25, U18.27, U18.28, U18.29, U18.31, U18.33, U18.61, U18.62, U18.65, U18.69
RFGND18: C112.2, JP129.GND@0, JP129.GND@1, JP129.GND@2, JP129.GND@3, R112.2, U19.21, U19.22, U19.24, U19.25, U19.27, U19.28, U19.29, U19.31, U19.33, U19.61, U19.62, U19.65, U19.69
RFGND19: C118.2, JP136.GND@0, JP136.GND@1, JP136.GND@2, JP136.GND@3, R118.2, U20.21, U20.22, U20.24, U20.25, U20.27, U20.28, U20.29, U20.31, U20.33, U20.61, U20.62, U20.65, U20.69
RFGND20: C124.2, JP143.GND@0, JP143.GND@1, JP143.GND@2, JP143.GND@3, R124.2, U21.21, U21.22, U21.24, U21.25, U21.27, U21.28, U21.29, U21.31, U21.33, U21.61, U21.62, U21.65, U21.69
RFGND21: C130.2, JP150.GND@0, JP150.GND@1, JP150.GND@2, JP150.GND@3, R130.2, U22.21, U22.22, U22.24, U22.25, U22.27, U22.28, U22.29, U22.31, U22.33, U22.61, U22.62, U22.65, U22.69
RFGND22: C136.2, JP157.GND@0, JP157.GND@1, JP157.GND@2, JP157.GND@3, R136.2, U23.21, U23.22, U23.24, U23.25, U23.27, U23.28, U23.29, U23.31, U23.33, U23.61, U23.62, U23.65, U23.69
RFGND23: C142.2, JP164.GND@0, JP164.GND@1, JP164.GND@2, JP164.GND@3, R142.2, U24.21, U24.22, U24.24, U24.25, U24.27, U24.28, U24.29, U24.31, U24.33, U24.61, U24.62, U24.65, U24.69
RFGND24: C148.2, JP171.GND@0, JP171.GND@1, JP171.GND@2, JP171.GND@3, R148.2, U25.21, U25.22, U25.24, U25.25, U25.27, U25.28, U25.29, U25.31, U25.33, U25.61, U25.62, U25.65, U25.69
RFGND25: C154.2, JP178.GND@0, JP178.GND@1, JP178.GND@2, JP178.GND@3, R154.2, U26.21, U26.22, U26.24, U26.25, U26.27, U26.28, U26.29, U26.31, U26.33, U26.61, U26.62, U26.65, U26.69
RFGND26: C160.2, JP185.GND@0, JP185.GND@1, JP185.GND@2, JP185.GND@3, R160.2, U27.21, U27.22, U27.24, U27.25, U27.27, U27.28, U27.29, U27.31, U27.33, U27.61, U27.62, U27.65, U27.69
RFGND27: C166.2, JP192.GND@0, JP192.GND@1, JP192.GND@2, JP192.GND@3, R166.2, U28.21, U28.22, U28.24, U28.25, U28.27, U28.28, U28.29, U28.31, U28.33, U28.61, U28.62, U28.65, U28.69
RFGND28: C172.2, JP199.GND@0, JP199.GND@1, JP199.GND@2, JP199.GND@3, R172.2, U29.21, U29.22, U29.24, U29.25, U29.27, U29.28, U29.29, U29.31, U29.33, U29.61, U29.62, U29.65, U29.69
RFGND29: C178.2, JP206.GND@0, JP206.GND@1, JP206.GND@2, JP206.GND@3, R178.2, U30.21, U30.22, U30.24, U30.25, U30.27, U30.28, U30.29, U30.31, U30.33, U30.61, U30.62, U30.65, U30.69
RSTN: C3.1, R1.1, U1.1
RSTN1: C9.1, R5.1, U2.1
RSTN2: C15.1, R13.1, U3.1
RSTN3: C21.1, R19.1, U4.1
RSTN4: C27.1, R25.1, U5.1
RSTN5: C33.1, R31.1, U6.1
RSTN6: C39.1, R37.1, U7.1
RSTN7: C45.1, R43.1, U8.1
RSTN8: C51.1, R49.1, U9.1
RSTN9: C57.1, R55.1, U10.1
RSTN10: C63.1, R61.1, U11.1
RSTN11: C69.1, R67.1, U12.1
RSTN12: C75.1, R73.1, U13.1
RSTN13: C81.1, R79.1, U14.1
RSTN14: C87.1, R85.1, U15.1
RSTN15: C93.1, R91.1, U16.1
RSTN16: C99.1, R97.1, U17.1
RSTN17: C105.1, R103.1, U18.1
RSTN18: C111.1, R109.1, U19.1
RSTN19: C117.1, R115.1, U20.1
RSTN20: C123.1, R121.1, U21.1
RSTN21: C129.1, R127.1, U22.1
RSTN22: C135.1, R133.1, U23.1
RSTN23: C141.1, R139.1, U24.1
RSTN24: C147.1, R145.1, U25.1
RSTN25: C153.1, R151.1, U26.1
RSTN26: C159.1, R157.1, U27.1
RSTN27: C165.1, R163.1, U28.1
RSTN28: C171.1, R169.1, U29.1
RSTN29: C177.1, R175.1, U30.1
RX0: R6.1, U1.42
RX1: JP4.1, U1.52
RX01: JP1.4, R6.2
RX02: R12.1, U2.42
RX03: JP11.1, U2.52
RX04: JP8.4, R12.2
RX05: R18.1, U3.42
RX06: JP18.1, U3.52
RX07: JP15.4, R18.2
RX08: R24.1, U4.42
RX09: JP25.1, U4.52
RX10: JP22.4, R24.2
RX11: R30.1, U5.42
RX12: JP32.1, U5.52
RX13: JP29.4, R30.2
RX14: R36.1, U6.42
RX15: JP39.1, U6.52
RX16: JP36.4, R36.2
RX17: R42.1, U7.42
RX18: JP46.1, U7.52
RX19: JP43.4, R42.2
RX20: R48.1, U8.42
RX21: JP53.1, U8.52
RX22: JP50.4, R48.2
RX23: R54.1, U9.42
RX24: JP60.1, U9.52
RX25: JP57.4, R54.2
RX26: R60.1, U10.42
RX27: JP67.1, U10.52
RX28: JP64.4, R60.2
RX29: R66.1, U11.42
RX30: JP74.1, U11.52
RX31: JP71.4, R66.2
RX32: R72.1, U12.42
RX33: JP81.1, U12.52
RX34: JP78.4, R72.2
RX35: R78.1, U13.42
RX36: JP88.1, U13.52
RX37: JP85.4, R78.2
RX38: R84.1, U14.42
RX39: JP95.1, U14.52
RX40: JP92.4, R84.2
RX41: R90.1, U15.42
RX42: JP102.1, U15.52
RX43: JP99.4, R90.2
RX44: R96.1, U16.42
RX45: JP109.1, U16.52
RX46: JP106.4, R96.2
RX47: R102.1, U17.42
RX48: JP116.1, U17.52
RX49: JP113.4, R102.2
RX50: R108.1, U18.42
RX51: JP123.1, U18.52
RX52: JP120.4, R108.2
RX53: R114.1, U19.42
RX54: JP130.1, U19.52
RX55: JP127.4, R114.2
RX56: R120.1, U20.42
RX57: JP137.1, U20.52
RX58: JP134.4, R120.2
RX59: R126.1, U21.42
RX60: JP144.1, U21.52
RX61: JP141.4, R126.2
RX62: R132.1, U22.42
RX63: JP151.1, U22.52
RX64: JP148.4, R132.2
RX65: R138.1, U23.42
RX66: JP158.1, U23.52
RX67: JP155.4, R138.2
RX68: R144.1, U24.42
RX69: JP165.1, U24.52
RX70: JP162.4, R144.2
RX71: R150.1, U25.42
RX72: JP172.1, U25.52
RX73: JP169.4, R150.2
RX74: R156.1, U26.42
RX75: JP179.1, U26.52
RX76: JP176.4, R156.2
RX77: R162.1, U27.42
RX78: JP186.1, U27.52
RX79: JP183.4, R162.2
RX80: R168.1, U28.42
RX81: JP193.1, U28.52
RX82: JP190.4, R168.2
RX83: R174.1, U29.42
RX84: JP200.1, U29.52
RX85: JP197.4, R174.2
RX86: R180.1, U30.42
RX87: JP207.1, U30.52
RX88: JP204.4, R180.2
SCL: JP4.3, U1.46
SCL1: JP11.3, U2.46
SCL2: JP18.3, U3.46
SCL3: JP25.3, U4.46
SCL4: JP32.3, U5.46
SCL5: JP39.3, U6.46
SCL6: JP46.3, U7.46
SCL7: JP53.3, U8.46
SCL8: JP60.3, U9.46
SCL9: JP67.3, U10.46
SCL10: JP74.3, U11.46
SCL11: JP81.3, U12.46
SCL12: JP88.3, U13.46
SCL13: JP95.3, U14.46
SCL14: JP102.3, U15.46
SCL15: JP109.3, U16.46
SCL16: JP116.3, U17.46
SCL17: JP123.3, U18.46
SCL18: JP130.3, U19.46
SCL19: JP137.3, U20.46
SCL20: JP144.3, U21.46
SCL21: JP151.3, U22.46
SCL22: JP158.3, U23.46
SCL23: JP165.3, U24.46
SCL24: JP172.3, U25.46
SCL25: JP179.3, U26.46
SCL26: JP186.3, U27.46
SCL27: JP193.3, U28.46
SCL28: JP200.3, U29.46
SCL29: JP207.3, U30.46
SDA: JP4.4, U1.45
SDA1: JP11.4, U2.45
SDA2: JP18.4, U3.45
SDA3: JP25.4, U4.45
SDA4: JP32.4, U5.45
SDA5: JP39.4, U6.45
SDA6: JP46.4, U7.45
SDA7: JP53.4, U8.45
SDA8: JP60.4, U9.45
SDA9: JP67.4, U10.45
SDA10: JP74.4, U11.45
SDA11: JP81.4, U12.45
SDA12: JP88.4, U13.45
SDA13: JP95.4, U14.45
SDA14: JP102.4, U15.45
SDA15: JP109.4, U16.45
SDA16: JP116.4, U17.45
SDA17: JP123.4, U18.45
SDA18: JP130.4, U19.45
SDA19: JP137.4, U20.45
SDA20: JP144.4, U21.45
SDA21: JP151.4, U22.45
SDA22: JP158.4, U23.45
SDA23: JP165.4, U24.45
SDA24: JP172.4, U25.45
SDA25: JP179.4, U26.45
SDA26: JP186.4, U27.45
SDA27: JP193.4, U28.45
SDA28: JP200.4, U29.45
SDA29: JP207.4, U30.45
TX0: JP1.3, U1.44
TX1: JP4.2, U1.57
TX2: JP8.3, U2.44
TX3: JP11.2, U2.57
TX4: JP15.3, U3.44
TX5: JP18.2, U3.57
TX6: JP22.3, U4.44
TX7: JP25.2, U4.57
TX8: JP29.3, U5.44
TX9: JP32.2, U5.57
TX10: JP36.3, U6.44
TX11: JP39.2, U6.57
TX12: JP43.3, U7.44
TX13: JP46.2, U7.57
TX14: JP50.3, U8.44
TX15: JP53.2, U8.57
TX16: JP57.3, U9.44
TX17: JP60.2, U9.57
TX18: JP64.3, U10.44
TX19: JP67.2, U10.57
TX20: JP71.3, U11.44
TX21: JP74.2, U11.57
TX22: JP78.3, U12.44
TX23: JP81.2, U12.57
TX24: JP85.3, U13.44
TX25: JP88.2, U13.57
TX26: JP92.3, U14.44
TX27: JP95.2, U14.57
TX28: JP99.3, U15.44
TX29: JP102.2, U15.57
TX30: JP106.3, U16.44
TX31: JP109.2, U16.57
TX32: JP113.3, U17.44
TX33: JP116.2, U17.57
TX34: JP120.3, U18.44
TX35: JP123.2, U18.57
TX36: JP127.3, U19.44
TX37: JP130.2, U19.57
TX38: JP134.3, U20.44
TX39: JP137.2, U20.57
TX40: JP141.3, U21.44
TX41: JP144.2, U21.57
TX42: JP148.3, U22.44
TX43: JP151.2, U22.57
TX44: JP155.3, U23.44
TX45: JP158.2, U23.57
TX46: JP162.3, U24.44
TX47: JP165.2, U24.57
TX48: JP169.3, U25.44
TX49: JP172.2, U25.57
TX50: JP176.3, U26.44
TX51: JP179.2, U26.57
TX52: JP183.3, U27.44
TX53: JP186.2, U27.57
TX54: JP190.3, U28.44
TX55: JP193.2, U28.57
TX56: JP197.3, U29.44
TX57: JP200.2, U29.57
TX58: JP204.3, U30.44
TX59: JP207.2, U30.57
VBAT: C5.1, C7.+, JP2.1, R3.2, U1.18
VBAT1: C11.+, C12.1, JP12.1, R11.2, U2.18
VBAT2: C17.+, C18.1, JP19.1, R17.2, U3.18
VBAT3: C23.+, C24.1, JP26.1, R23.2, U4.18
VBAT4: C29.+, C30.1, JP33.1, R29.2, U5.18
VBAT5: C35.+, C36.1, JP40.1, R35.2, U6.18
VBAT6: C41.+, C42.1, JP47.1, R41.2, U7.18
VBAT7: C47.+, C48.1, JP54.1, R47.2, U8.18
VBAT8: C53.+, C54.1, JP61.1, R53.2, U9.18
VBAT9: C59.+, C60.1, JP68.1, R59.2, U10.18
VBAT10: C65.+, C66.1, JP75.1, R65.2, U11.18
VBAT11: C71.+, C72.1, JP82.1, R71.2, U12.18
VBAT12: C77.+, C78.1, JP89.1, R77.2, U13.18
VBAT13: C83.+, C84.1, JP96.1, R83.2, U14.18
VBAT14: C89.+, C90.1, JP103.1, R89.2, U15.18
VBAT15: C95.+, C96.1, JP110.1, R95.2, U16.18
VBAT16: C101.+, C102.1, JP117.1, R101.2, U17.18
VBAT17: C107.+, C108.1, JP124.1, R107.2, U18.18
VBAT18: C113.+, C114.1, JP131.1, R113.2, U19.18
VBAT19: C119.+, C120.1, JP138.1, R119.2, U20.18
VBAT20: C125.+, C126.1, JP145.1, R125.2, U21.18
VBAT21: C131.+, C132.1, JP152.1, R131.2, U22.18
VBAT22: C137.+, C138.1, JP159.1, R137.2, U23.18
VBAT23: C143.+, C144.1, JP166.1, R143.2, U24.18
VBAT24: C149.+, C150.1, JP173.1, R149.2, U25.18
VBAT25: C155.+, C156.1, JP180.1, R155.2, U26.18
VBAT26: C161.+, C162.1, JP187.1, R161.2, U27.18
VBAT27: C167.+, C168.1, JP194.1, R167.2, U28.18
VBAT28: C173.+, C174.1, JP201.1, R173.2, U29.18
VBAT29: C179.+, C180.1, JP208.1, R179.2, U30.18

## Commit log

2015-05-01 Adding hardware files, updating README
2015-10-16 Updated PWR-RF GND jumper to fix Eagle issue
    The Venus has power and rf grounds that should only connect at one place
    on the board (R7). There was an issue with Eagle not automatically
    connecting to this ground, leaving airwires. Part updated and overt
    traces added.
2015-10-19 created new panel v21
